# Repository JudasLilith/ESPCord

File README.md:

## ESPCord

* An ESP32-based  PCB to connect to Wall adapters for controlling power to SBCs.

### Why make this?

* I normally use a small Raspberry Pi Zero in order for me to control my Octoprint setup, but due to the board being connected constantly it cannot shut down with the normal octoprint UI. This is when I thought that I should have a method of controlling the power going to the Setup, so that it can properly reboot every time I manipulate its power source by being connected to Home Assistant.

* ### Don't you have wall plugs that do this?

  * You're absolutely right! however:
    * The prices are at least 30 dollars a pop
    * most of the cheaper ones want you to use their own crummy software
    * It's closed source(yuck!)
    * most of them connect to wall sockets, so if you move between countries where one uses 110 and the other uses 220, it's better to just connect from the wall adapter itself(since you know that the voltage coming from there is a regulated 5v.)

### Images

### How to Make one:

**WARNING!** The USB and the actual power supply coming from the wires are synonymous, so I do not recommend connecting the Power pins and the USB to flash the program at the same time.

* The step files for the cover are in hardware/STEP. For each of the PCB's models, it's inside /hardware/ESPCord/JLCImport.3dshapes/.

* Go to OnShape for the source files: [Link to Document](https://cad.onshape.com/documents/d3868ff451e5f7abe82f5476/w/f427325b5d68ac91fa5e3531/e/b186e742c5d57084cca7bd3f?renderMode=0&rightPanel=explodedViewPanel&uiState=6a36acb3a9f4b17da6166d23)

#### BOM:

For the Detailed version with comments, look at the BOM.csv

|           |     |                      |        |                                      |
| --------- | --- | -------------------- | ------ | ------------------------------------ |
| Reference | Qty | Value                | Price  | Footprint                            |
| C1,C2     | 2   | 10uF_0805_16V_lowESR | 0.091  | PCM_4ms_Capacitor:C_0805             |
| J1        | 1   | USB_C_Receptacle     | 0.05   | PCM_SparkFun-Connector:USB-C_16      |
| K1        | 1   | SRD-03VDC-SL-C       | 0.41   | JLCImport:SRD-03VDC-SL-C             |
| R3,R4     | 2   | 5.1K                 | 0.02   | PCM_fab:R_1206                       |
| U1        | 1   | ESP32-C3             | 1.83   | PCM_fab:QFN-32_EP_5x5_Pitch0.5mm     |
| U2        | 1   | AMS1117-3_3_C347222  | 0.01   | PCM_Package_TO_SOT_SMD_AKL:SOT-223-5 |
|           |     |                      | 0      |                                      |
|           | 4   | M3 Bolts 10mm        | 19.99  | N/A                                  |
|           | 2   | M2 Bolts 25mm        | 0      | N/A                                  |
|           | 4   | M3 Nuts              | 0      | N/A                                  |
|           | 2   | m2 Nuts              | 0      | N/A                                  |
|           |     |                      |        |                                      |
|           |     | Total:               | 22.351 |                                      |
					
		Total:	22.351		

* The case has around 12 grams of PLA, so it's most likely negligible.

### For the design checker: I already have a kit with M2-M3 bolts and nuts, so the amazon kit will be redundant in my case. I just wantd to show where other people could source the parts in bulk.

#### Assembly:

#### Whole Model:

### Next Steps:

* Time to actually connect the relay with the power cables now.

* Now all you need to do is:

  * Split the cable in half
  * Find the Red and Black wires, then solder them onto each pads with the Label GND and VIN.
  * Be sure that the nuts do not touch, if using bare metal nuts and bolts.

* Great job following along! now you must flash the ESP with ESPHome.
(You can find more information at: https://esphome.io/guides/getting_started_hassio/)

* I tried to make a simple configuration file in /firmware, but it's not tested yet so take it with a grain of salt please :3

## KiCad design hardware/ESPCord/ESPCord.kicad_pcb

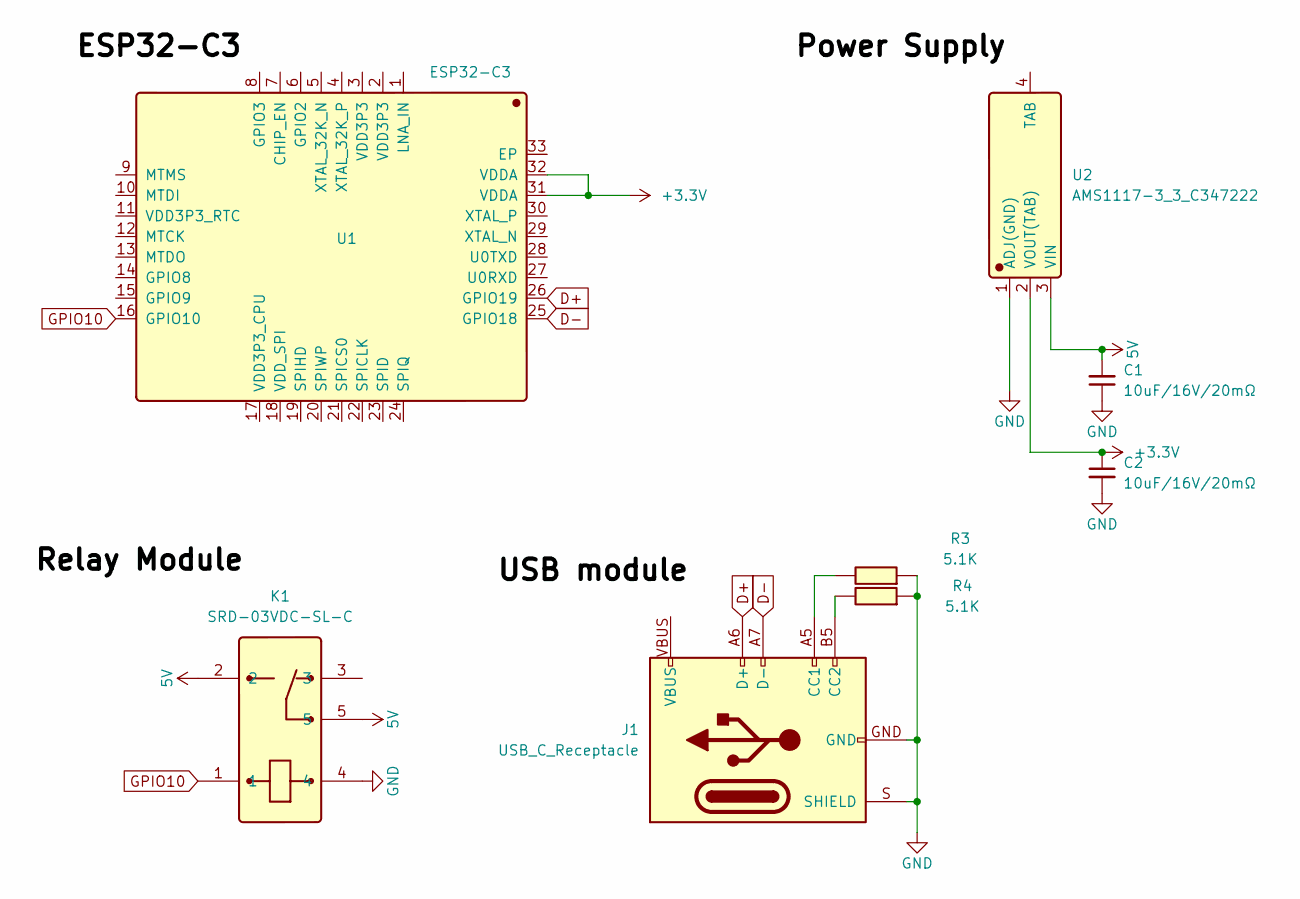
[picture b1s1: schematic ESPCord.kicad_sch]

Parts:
C1, C2: 10uF_0805_16V_lowESR; C_0805; Part Number EMK212ABJ106KG-T; JLCPCB ID C190442
J1: USB_C_Receptacle; USB-C_16
K1: SRD-03VDC-SL-C; Manufacturer Part SRD-03VDC-SL-C; LCSC C24585
R3, R4: 5.1K; R_1206
U1: ESP32-C3; QFN-32_EP_5x5_Pitch0.5mm; Manufacturer Part ESP32-C3; LCSC C2838500
U2: AMS1117-3_3_C347222; SOT-223-5; Manufacturer Part AMS1117-3.3; LCSC C347222

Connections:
5V: C1.2, K1.2, K1.5, U2.3 (VIN)
+3.3V: C2.1, U1.31 (VDDA), U1.32 (VDDA), U2.2 (VOUT(TAB))
D+: J1.A6 (D+), J1.B6 (D+), U1.26 (GPIO19)
D-: J1.A7 (D-), J1.B7 (D-), U1.25 (GPIO18)
GND: C1.1, C2.2, J1.GND, J1.S (SHIELD), K1.4, R3.2, R4.2, U2.1 (ADJ(GND))
GPIO10: K1.1, U1.16 (GPIO10)
unnamed: J1.A5 (CC1), R3.1
unnamed: J1.B5 (CC2), R4.1

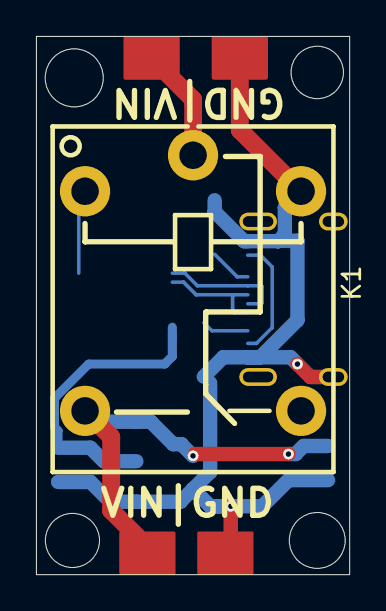
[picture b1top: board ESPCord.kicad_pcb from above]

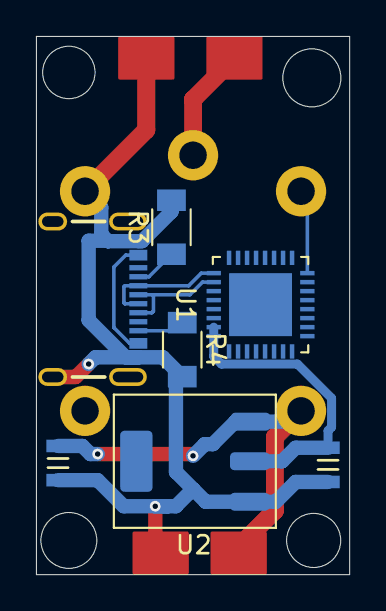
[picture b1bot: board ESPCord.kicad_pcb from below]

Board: 2 copper layers, 17.4 x 29.9 mm, 8 parts (7 on the bottom side), 8 nets.

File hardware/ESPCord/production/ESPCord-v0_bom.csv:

Designator,Footprint,Quantity,Value,LCSC Part #
"C1, C2",C_0805,2,10uF_0805_16V_lowESR,
J1,USB-C_16,1,USB_C_Receptacle,
K1,SRD-03VDC-SL-C,1,SRD-03VDC-SL-C,C24585
"R3, R4",R_1206,2,5.1K,C881294
U1,QFN-32_EP_5x5_Pitch0.5mm,1,ESP32-C3,C2838500
U2,SOT-223-5,1,AMS1117-3_3_C347222,C347222

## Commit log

2026-06-20 added the pcb, and now time to work on the Zine along with programming
2026-06-21 worked on everuthing, it's set now
2026-06-21 .pretty files and step files got srewed, adding them again
2026-06-21 removed .csv from gitignore
2026-06-21 added BOM
2026-06-21 added BOM inside repo, again
2026-06-24 final touches, thickened the routes and altered zine
2026-06-25 fixed up the zine, now everything is finished :sob
2026-06-26 fixed the BOM
2026-06-26 altered zine, fingers crossed
2026-06-26 altered the BOM, finally
    the end is here
2026-06-26 just added the pcb cost, mb
